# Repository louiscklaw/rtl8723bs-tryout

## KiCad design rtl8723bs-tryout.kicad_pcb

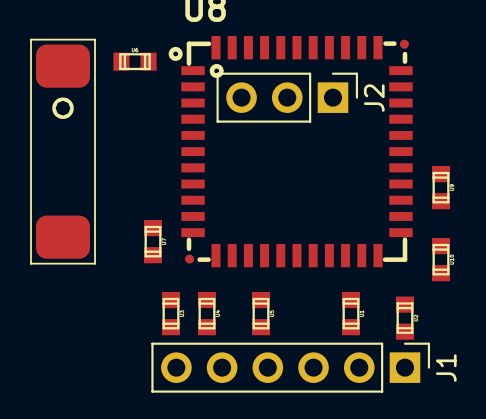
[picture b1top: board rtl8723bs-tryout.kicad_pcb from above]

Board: 2 copper layers, 13 parts (0 on the bottom side), 16 nets, no tracks yet.

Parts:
AE1: Antenna_Shield; rainsun-AN9520
J1: SDC_DEBUG; PinHeader_1x06_P2.54mm_Vertical
J2: UART_DEBUG; PinHeader_1x03_P2.54mm_Vertical
U1, U2, U3, U4, U5: 47KΩ,(4702),±1%,0603,C25819; r_0603
U6: 33pF,(330),±5%,50V,C0G,0603,C1663; c_0603
U7, U9: 100KΩ,(1003),±1%,0603,C25803; r_0603
U8: RTL8723BS; RL-SM02BD(RTL8723BS)
U10: 10KΩ,(1002),±1%,0603,C25804; r_0603

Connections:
+3V3: U1.2, U2.2, U3.2, U4.2, U5.2, U7.2, U8.9, U8.22, U9.1, U10.1
/SDC1_CLK: J1.3, U8.17
/SDC1_CMD: J1.4, U5.1, U8.16
/SDC1_D0: J1.2, U1.1, U8.18
/SDC1_D1: J1.1, U2.1, U8.19
/SDC1_D2: J1.6, U3.1, U8.14
/SDC1_D3: J1.5, U4.1, U8.15
GND: U8.1, U8.3, U8.20, U8.31, U8.33, U8.36, U8.41
unnamed: AE1.1, U6.2
unnamed: J2.1, U8.42
unnamed: J2.2, U8.43
unnamed: J2.3, U8.44
unnamed: U6.1, U8.2
unnamed: U7.1, U8.12
unnamed: U8.34, U9.2
unnamed: U8.23, U10.2

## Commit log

2020-02-28 init commit,
2020-04-25 add footprint photo,
2020-04-25 init travis.yml,
2020-04-25 update,
2020-04-25 add to ignore bak files,
2020-04-25 update footprint,
2020-04-25 update footprint arrangement,
2020-04-25 update cache,
2020-04-25 adding credentials,
